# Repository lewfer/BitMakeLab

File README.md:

# BitMakeLab
Resources for Digital Makers

[BitMakeLab Website](https://www.thinkcreatelearn.co.uk/resources/bitmakelab)

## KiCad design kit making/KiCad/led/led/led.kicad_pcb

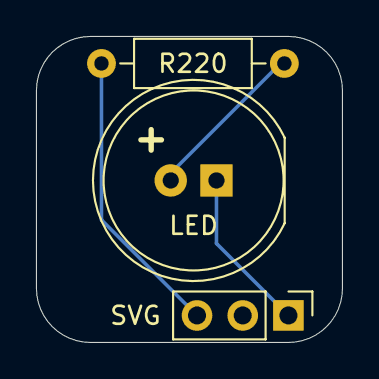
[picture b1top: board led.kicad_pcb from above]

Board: 2 copper layers, 17.0 x 17.0 mm, 3 parts (0 on the bottom side), 3 nets.

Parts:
LED: LED; LED_D10.0mm
R220: 220; R_Axial_DIN0207_L6.3mm_D2.5mm_P10.16mm_Horizontal
SVG: Conn_01x03_Pin; PinHeader_1x03_P2.54mm_Vertical

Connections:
/GND: LED.1 (K), SVG.1
/LED: LED.2 (A), R220.1
/SIGNAL: R220.2, SVG.3

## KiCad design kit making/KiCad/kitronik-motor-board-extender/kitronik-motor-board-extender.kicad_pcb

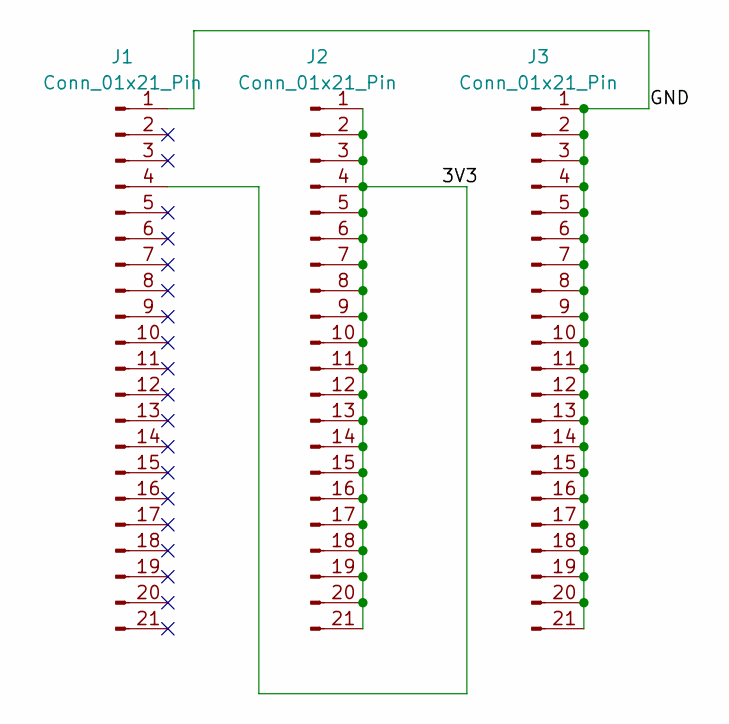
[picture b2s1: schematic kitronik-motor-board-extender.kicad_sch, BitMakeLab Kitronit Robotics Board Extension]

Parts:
J1, J2, J3: Conn_01x21_Pin; PinHeader_1x21_P2.54mm_Vertical

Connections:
/3V3: J1.4, J2.1, J2.2, J2.3, J2.4, J2.5, J2.6, J2.7, J2.8, J2.9, J2.10, J2.11, J2.12, J2.13, J2.14, J2.15, J2.16, J2.17, J2.18, J2.19, J2.20, J2.21
/GND: J1.1, J3.1, J3.2, J3.3, J3.4, J3.5, J3.6, J3.7, J3.8, J3.9, J3.10, J3.11, J3.12, J3.13, J3.14, J3.15, J3.16, J3.17, J3.18, J3.19, J3.20, J3.21

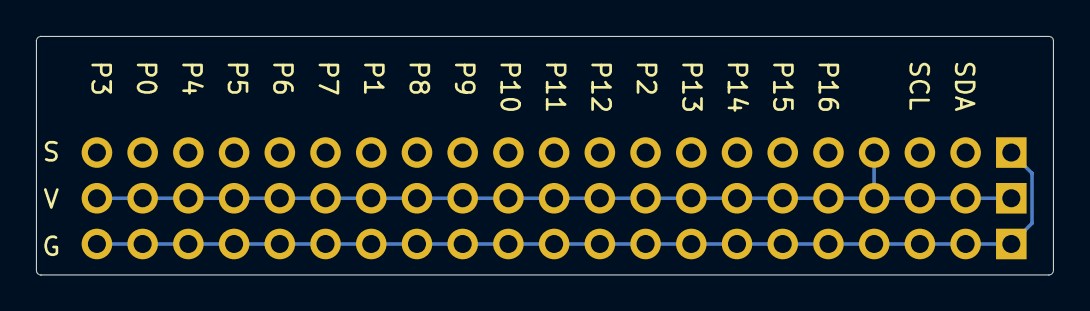
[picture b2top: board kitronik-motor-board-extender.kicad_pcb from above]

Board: 2 copper layers, 56.5 x 13.2 mm, 3 parts (0 on the bottom side), 2 nets.

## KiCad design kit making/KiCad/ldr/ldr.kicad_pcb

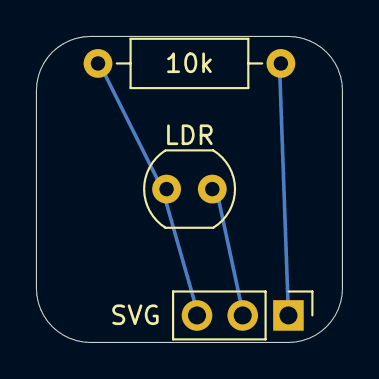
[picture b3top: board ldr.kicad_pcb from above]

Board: 2 copper layers, 17.0 x 17.0 mm, 3 parts (0 on the bottom side), 3 nets, no tracks yet.

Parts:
10k: R; R_Axial_DIN0207_L6.3mm_D2.5mm_P10.16mm_Horizontal
LDR: VT93xx; R_LDR_4.9x4.2mm_P2.54mm_Vertical
SVG: Conn_01x03_Pin; PinHeader_1x03_P2.54mm_Vertical

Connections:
/3v3: LDR.1, SVG.2
/GND: 10k.2, SVG.1
/SIGNAL: 10k.1, LDR.2, SVG.3

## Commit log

2024-04-22 Update LICENSE
2024-04-22 Intial
2024-04-29 tidied
2024-04-29 Added intro and tutor notes
2024-05-03 Updated worksheets
2024-05-03 test
2024-05-03 Reorganised
2024-05-03 Rename introductions
2024-05-03 Moved introductions
2024-05-03 Organised tutor notes
2024-05-03 Reorganised to align with website
2024-05-23 Added kicad projects
2024-09-15 Updated 3d parts and started migrating to DF robot motor board
2024-10-24 Worksheet updates, box inserts, updated controller code
2024-10-25 Filename correction
2025-02-24 various
2025-03-03 Updated ultrasonic to df robot
2025-05-27 Added train projects and started reference
2025-05-27 Renamed
